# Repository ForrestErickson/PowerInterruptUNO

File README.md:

# PowerInterruptUNO
## A power interrupt test device biased on UNO shield.  
For some time I have wished for a test system to interupt power, make power drop outs, of programable length to stress test micro controller based systems against unreliable reset in the cases of power interupt. I had ideas for years and finaly put something on my white board back during the early days of COVID when I was in my lab doing long over due continuing education and haunting the FaceBook groups for Arduino and ESP. I was struck how many persons were having trouble with systems not staring reliably and noticed that many micro controller development boards did not have a diode to discharge the /Reset line on a power drop out.

So I present, A shield which will switch or interrupt power to a DUT. The power comes in on a 2.1mm barrel jack and goes out on screw terminals, USB Type A connector and USB type C and on an RJ12.

The white board schematic that started it ?last year or earlier?.
KiCad 6 schematic started 20220714 about 2:00 PM EDT.

The schematic

The component palcement

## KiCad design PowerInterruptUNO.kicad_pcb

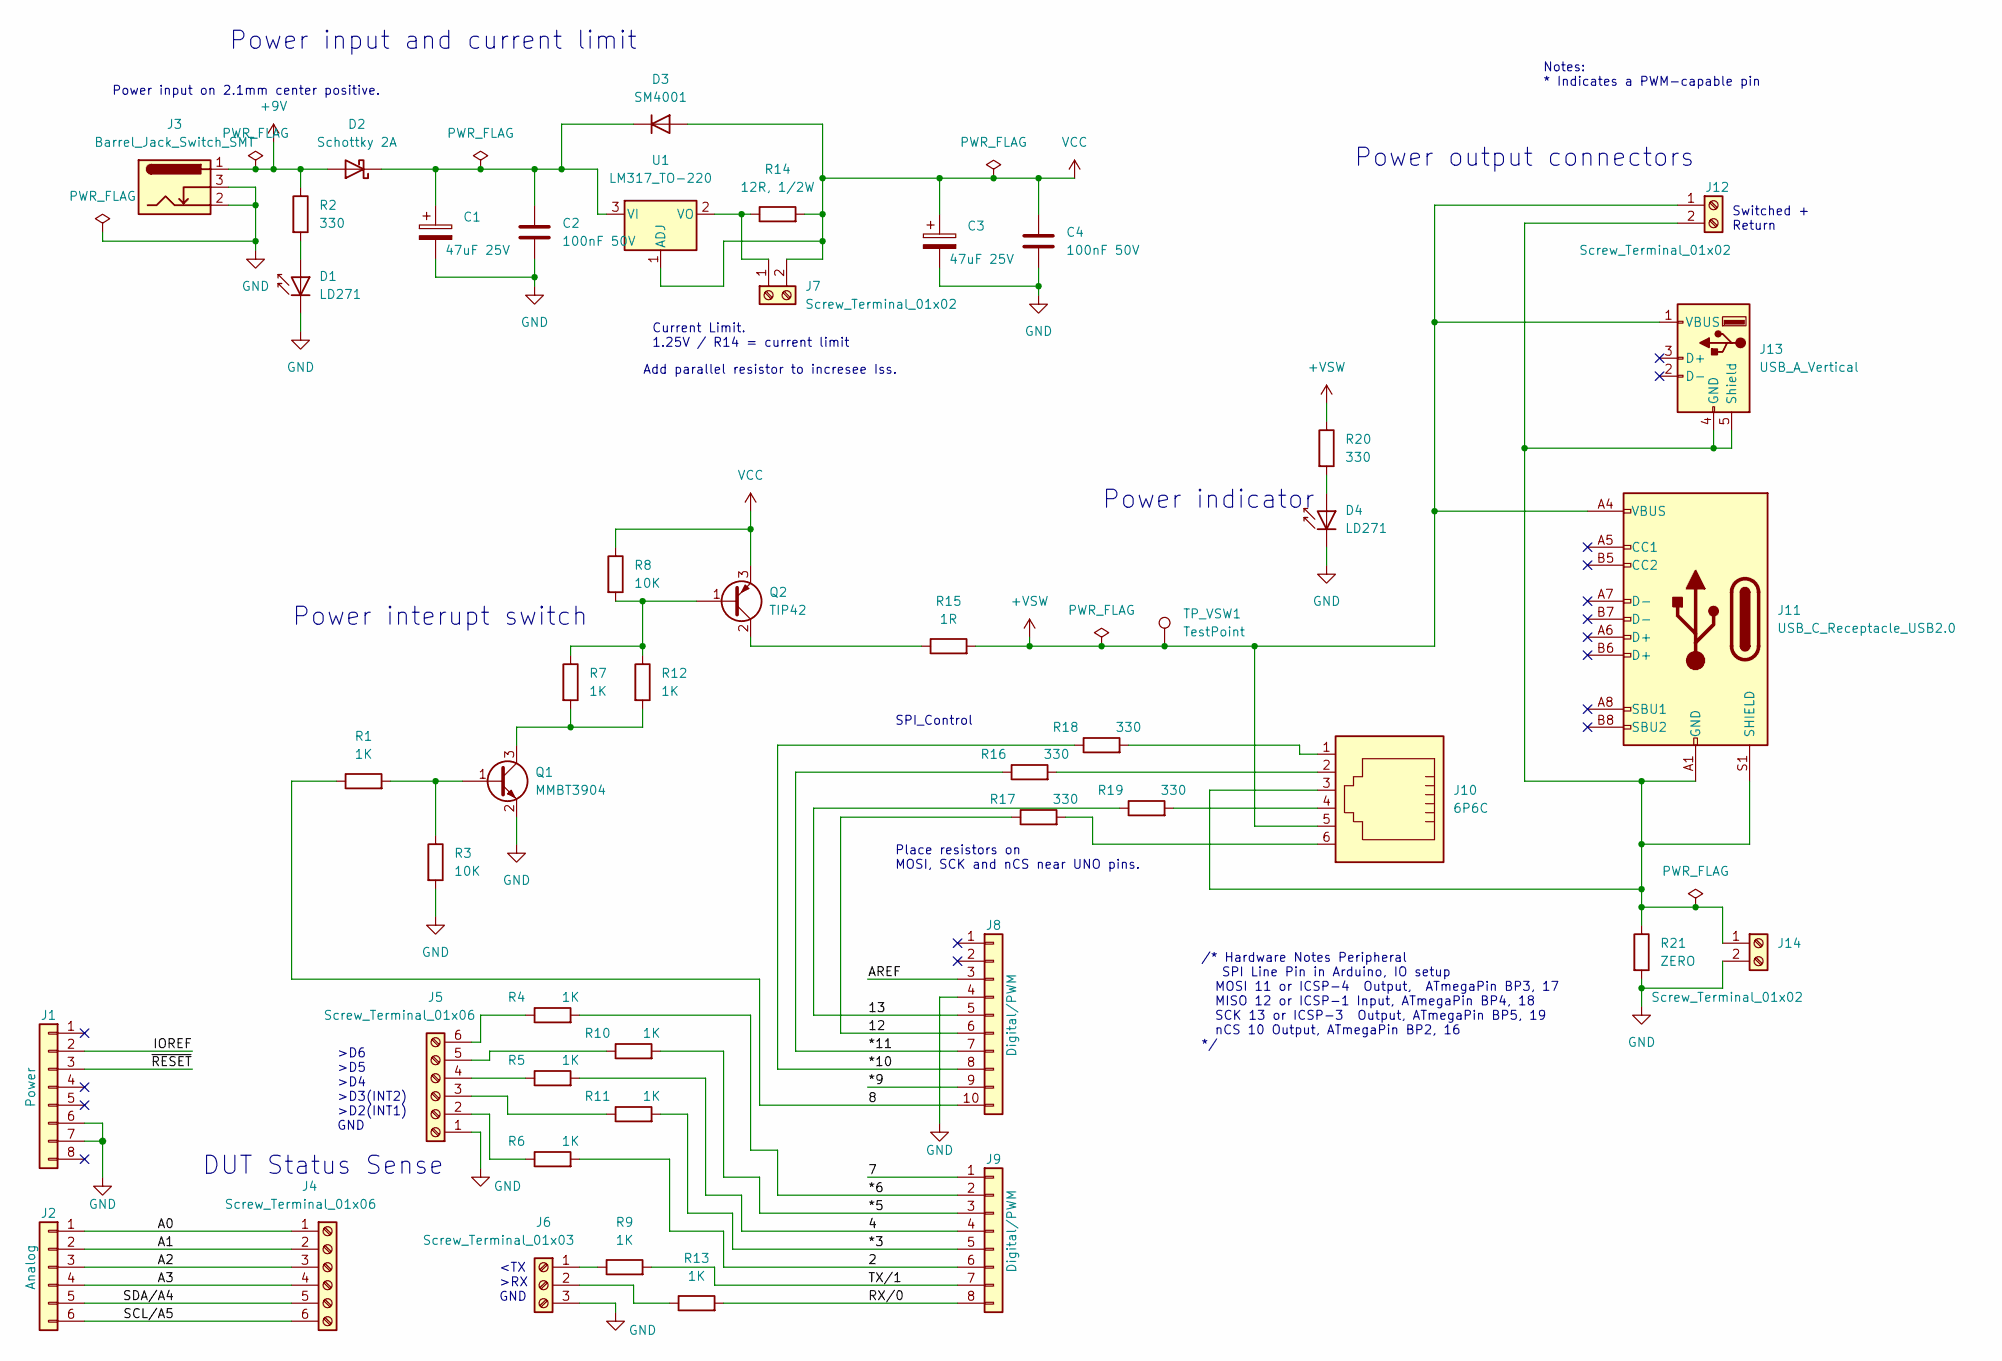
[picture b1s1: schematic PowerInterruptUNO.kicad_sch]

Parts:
C1, C3: 47uF 25V; CP_Elec_6.3x5.3; MPN RVT1E470M0605
C2, C4: 100nF 50V; C_0603_1608Metric_Pad1.08x0.95mm_HandSolder; MPN CC0603KRX7R9BB104
D1, D4: LD271; LED_0603_1608Metric_Pad1.05x0.95mm_HandSolder; MPN KT-0603R
D2: Schottky 2A; D_SMB; MPN SS210
D3: SM4001; D_MELF; MPN SM4001PL-TP
J1: Power; PinSocket_1x08_P2.54mm_Vertical; MPN foo
J2: Analog; PinSocket_1x06_P2.54mm_Vertical; MPN foo
J3: Barrel_Jack_Switch_SMT; BarrelJack_CLIFF_FC681465S_SMT_Horizontal; MPN XKB Connectivity / Tensility Internatio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
J4, J5: Screw_Terminal_01x06; TerminalBlock_TE_282834-6_1x06_P2.54mm_Horizontal; MPN DB125-2.54-6P-GN
J6: Screw_Terminal_01x03; TerminalBlock_TE_282834-3_1x03_P2.54mm_Horizontal; MPN DB125-2.54-3P-GN
J7, J12, J14: Screw_Terminal_01x02; TerminalBlock_TE_282834-2_1x02_P2.54mm_Horizontal; MPN DB125-2.54-2P-GN
J8: Digital/PWM; PinSocket_1x10_P2.54mm_Vertical; MPN foo
J9: Digital/PWM; PinSocket_1x08_P2.54mm_Vertical; MPN foo
J10: 6P6C; RJ12_Amphenol_54601; MPN 5555165-1
J11: USB_C_Receptacle_USB2.0; USB_C_Receptacle_XKB_U262-16XN-4BVC11; MPN U262-161N-4BVC11
J13: USB_A_Vertical; USB_A_Wuerth_614004134726_Horizontal; MPN C26235
Q1: MMBT3904; SOT-23; MPN MMBT3904
Q2: TIP42; TO-220-3_Vertical; MPN TIP42C
R1, R4, R5, R6, R7, R9, R10, R11, R12, R13: 1K; R_0603_1608Metric_Pad0.98x0.95mm_HandSolder; MPN RC0603FR-071KL
R2, R16, R17, R18, R19, R20: 330; R_0603_1608Metric_Pad0.98x0.95mm_HandSolder; MPN RC0603FR-07330RL
R3, R8: 10K; R_0603_1608Metric_Pad0.98x0.95mm_HandSolder; MPN RC0603JR-0710KL
R14: 12R, 1/2W; R_Axial_DIN0414_L11.9mm_D4.5mm_P25.40mm_Horizontal; MPN foo
R15: 1R; R_0603_1608Metric_Pad0.98x0.95mm_HandSolder; MPN foo
R21: ZERO; R_0603_1608Metric_Pad0.98x0.95mm_HandSolder; MPN foo
TP_VSW1: TestPoint; TestPoint_Loop_D2.50mm_Drill1.85mm; MPN foo
U1: LM317_TO-220; TO-220-3_Vertical; MPN LM317KCT

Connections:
+9V: D2.2 (A), J3.1, R2.1
+VSW: J10.5, J11.A4 (VBUS), J11.A9 (VBUS), J11.B4 (VBUS), J11.B9 (VBUS), J12.1, J13.1 (VBUS), R15.2, R20.1, TP_VSW1.1
/2: J9.6, R6.2
/4: J9.4, R5.2
/7: J9.1
/8: J8.10, R1.1
/12: J8.6, R17.1
/13: J8.5, R19.1
/*3: J9.5, R11.2
/*5: J9.3, R10.2
/*6: J9.2, R4.2
/*9: J8.9
/*10: J8.8, R18.1
/*11: J8.7, R16.1
/A0: J2.1, J4.1
/A1: J2.2, J4.2
/A2: J2.3, J4.3
/A3: J2.4, J4.4
/AREF: J8.3
/IOREF: J1.2
/RX/0: J9.8, R13.2
/SCL/A5: J2.6, J4.6
/SDA/A4: J2.5, J4.5
/TX/1: J9.7, R9.2
/~RESET: J1.3
GND: C1.2, C2.2, C3.2, C4.2, D1.1 (K), D4.1 (K), J1.6, J1.7, J3.2, J3.3, J5.1, J6.3, J8.4, J14.2, Q1.2 (E), R3.2, R21.2
unnamed: C1.1, C2.1, D2.1 (K), D3.1 (K), U1.3 (VI)
unnamed: D1.2 (A), R2.2
unnamed: D4.2 (A), R20.2
unnamed: J5.2, R6.1
unnamed: J5.3, R11.1
unnamed: J5.4, R5.1
unnamed: J5.5, R10.1
unnamed: J5.6, R4.1
unnamed: J6.1, R9.1
unnamed: J6.2, R13.1
unnamed: J7.1, R14.1, U1.2 (VO)
unnamed: J10.1, R18.2
unnamed: J10.2, R16.2
unnamed: J10.3, J11.A1 (GND), J11.A12 (GND), J11.B1 (GND), J11.B12 (GND), J11.S1 (SHIELD), J12.2, J13.4 (GND), J13.5 (Shield), J14.1, R21.1
unnamed: J10.4, R19.2
unnamed: J10.6, R17.2
unnamed: Q1.1 (B), R1.2, R3.1
unnamed: Q1.3 (C), R7.2, R12.2
unnamed: Q2.1 (B), R7.1, R8.2, R12.1
unnamed: Q2.2 (C), R15.1
VCC: C3.1, C4.1, D3.2 (A), J7.2, Q2.3 (E), R8.1, R14.2, U1.1 (ADJ)

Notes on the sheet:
Power output connectors
Power input on 2.1mm center positive.
Power interupt switch
Place resistors on MOSI, SCK and nCS near UNO pins.
Power indicator
Add parallel resistor to incresee Iss.
SPI_Control
Current Limit. 1.25V / R14 = current limit
Power input and current limit
DUT Status Sense
Switched + Return
<TX >RX GND
Notes: * Indicates a PWM-capable pin
>D6 >D5 >D4 >D3(INT2) >D2(INT1) GND
/* Hardware Notes Peripheral SPI Line Pin in Arduino, IO setup MOSI 11 or ICSP-4 Output, ATmegaPin BP3, 17 MISO 12 or ICSP-1 Input, ATmegaPin BP4, 18 SCK 13 or ICSP-3 Output, ATmegaPin BP5, 19 nCS 10 Output, ATmegaPin BP2, 16 */

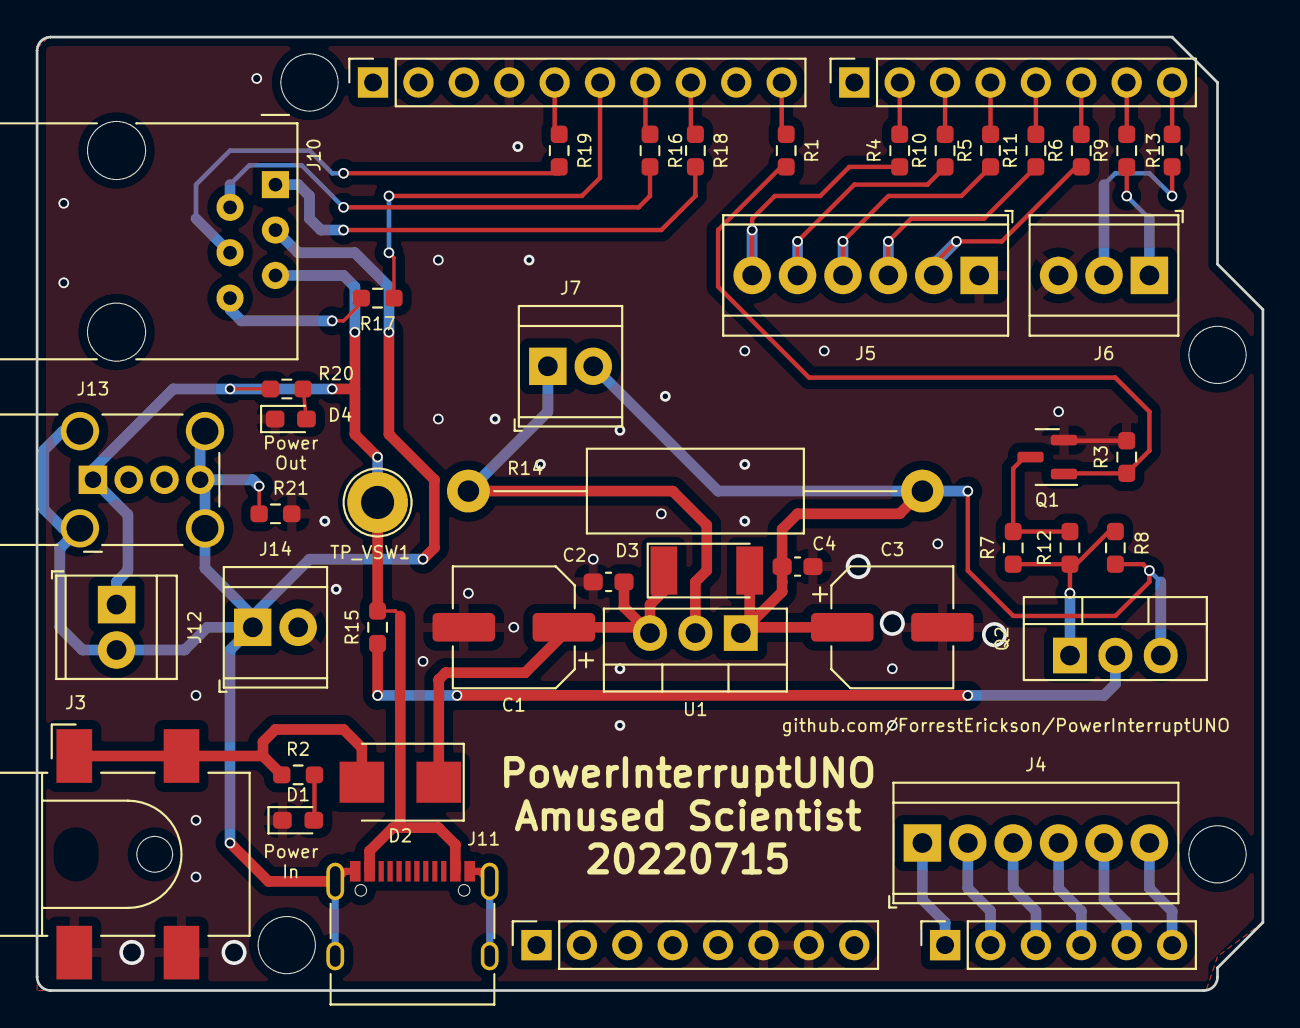
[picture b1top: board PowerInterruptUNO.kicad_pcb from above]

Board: 2 copper layers, 68.6 x 53.3 mm, 51 parts (0 on the bottom side), 42 nets.

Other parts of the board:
MH1, MH2, MH3, MH4: MountingHole_3.2mm

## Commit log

2022-07-14 Initial commit of an UNO project from a template.
2022-07-14 Rough out schematic for power in. Current limit. Switched power to terminal, USBA, USBC, RJ12 SPI Controler. Inputs terminals for interupt and ADC.
2022-07-14 Annote schematic.
2022-07-14 Clear electrical rules check on schematic.
2022-07-14 Add JLCPCB part numberes to some components.
2022-07-15 Place parts on PCB.
2022-07-15 Add photo of white board circuit.
2022-07-15 Create README.md
    Start the readme.
2022-07-15 Add screen shots of Schematic and PCB with placed components.
2022-07-15 Update README.md
    Add screen shots of Schematic and PCB with placed components.'
2022-07-15 Initial routing. 100% connected but lots of DRC errors to track down.
2022-07-15 Clear some DRC errors but many remaining including Silkscreen clipping solder mask.
2022-07-15 Update README.md
    Resize the white board image.
2022-07-15 Prior to moving J11 inboard
2022-07-15 Move J11. Change text size. Move a few other parts to help with text placement. Add visa to stich ground. DRC error related to double pads on J11 I can not clear. Do not think it is a problem (he foo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
